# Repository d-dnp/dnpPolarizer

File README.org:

#+TITLE: Dissolution-DNP Polarizer at Southampton University

* Project description
Dissolution-Dynamic Nuclear Polarization (d-DNP) is a technique to enhance the nuclear magnetic reosonance (NMR) signal of small molecules / metabolites by several orders of magnitude. 

Clinical and pre-clinical systems are available commercially, but are costly and cannot provide the felixibility to implement new experimental procedures.

This repository contains the design of the dissolution-DNP system at Southampton University. We hope that it will become a valuable ressource for people working in the field and would be grateful for external contributions / modifications.

Using Trityl and pyruvic acid, a polarization level of 18 % was achieved.

Using TEMPOL and H2O/d-glycerol, a polarization level of 12 % was achieved on sodium acetate.

* The setup at Southampton

The system operates at 6.7 Tesla and uses an Oxford Instruments Spectrostat flow cryostat and a roots pump.

The key components that we are using are as follows: 
| Component                 | Manufacturer       | Approximate Price (EURO)            |
|---------------------------+--------------------+-------------------------------------|
| 6.7 Tesla SWB Magnet      | Bruker             | 60 k (used WB magnets are suitable) |
| Spectrostat Flow Cryostat | Oxford Instruments | 20 k                                |
| Roots Pump, RUVAC WAU251  | Oerlikon           | 20 k                                |
| 188 GHz Microwave Source  | ELVA               | 20 k                                |
| Mini NMR Spectrometer     | Magritek           | 20 k                                |

The use of the Spectrostat Flow cryostat currently limits the temperature to above 2.1 K in continuous mode and 1.8 K in single-shot mode (hold-time approximately 45 mins). 

Options for cryostats with lower base temperature are currently being explored.

** Custom-built components

In addition to these componets, we have designed and built various pieces of instrumentation, listed below. We will shortly add a README file to each of the corresponding folders to provide further information. The mechanical design was performed in SolidWorks. The control electronics rely on the Arduino platform, for which custom printed-circuit board (PCB) extensions, referred to as shields, have been designed in Eagle. The radio-frequency design has been simulated in Python. The project is documented using Emacs org-mode. 

*** DNP insert and CryoShield
The dnp insert allows to irradiate the sample with microwaves at low temperatures down to 1.6K and measure its polarization by NMR. It also hosts a set of Allen-Bradley resistors attached to a custom-built controller/shield. This shield applies 5V pulses to the resistors and measures their resistance as function of time immediately after the pulse. Currently our insert is equipped with coils for 13C and 1H. The coils are roughly tuned and matched with ATC700B chip capacitors, fine tuning is done at room temperatures using an L-Network of Jennings capacitors 1.5 - 45 pF, and optionally coaxial line stretchers (trombone lines) by Microlab.

*** Dissolution Wand and Controller
The controller for the dissolution wand comprises a 220 V to 110 V transformer, whose output can be connected to a mineral barrel heater on the dissolution wand. It also hosts a custom shield that measures the temperature and pressure within the dissolution wand via simple voltage dividers. Finally the controller hosts a relay board to control the various (pilot) valves in the system, including those that drive the dissolution. 

*** Magnetic Tunnel
Following dissolution the solute is flushed to our 500 MHz liquid-state NMR magnet via a magnetic tunnel to reduce low-field relaxation. Documentation of the tunnel is to follow.

*** Injector
An injector has been designed to fit into our 500 MHz magnet. 

*** Arbitrary Waveform Generator
An arbitrary waveform generator providing an output of up to 24 V has been designed to allow sweeps of the microwave source. We are not using it routinely at the moment, though it is fully functional. 
This device is based on an Arduino Due.

* Procedures
** Sample preparation
More detailed procedures will be in the sample preparation folder.

** Probe tuning
We use an Agilent FieldFox Network Analyser to tune and match our probes. More details will be published soon.

* Acknowledgement
We would like to thank Sami Jannin, Jonas Milani, Jan Hendrik Ardenkjaer-Larsen, Arnaud Comment and Jacques van der Klink for discussions and advice.

* License
#+BEGIN_HTML
<br />This work is licensed under a <a rel="license" href="http://creativecommons.org/licenses/by-sa/3.0/">Creative Commons Attribution-ShareAlike 3.0 Unported License</a>.
#+END_HTML

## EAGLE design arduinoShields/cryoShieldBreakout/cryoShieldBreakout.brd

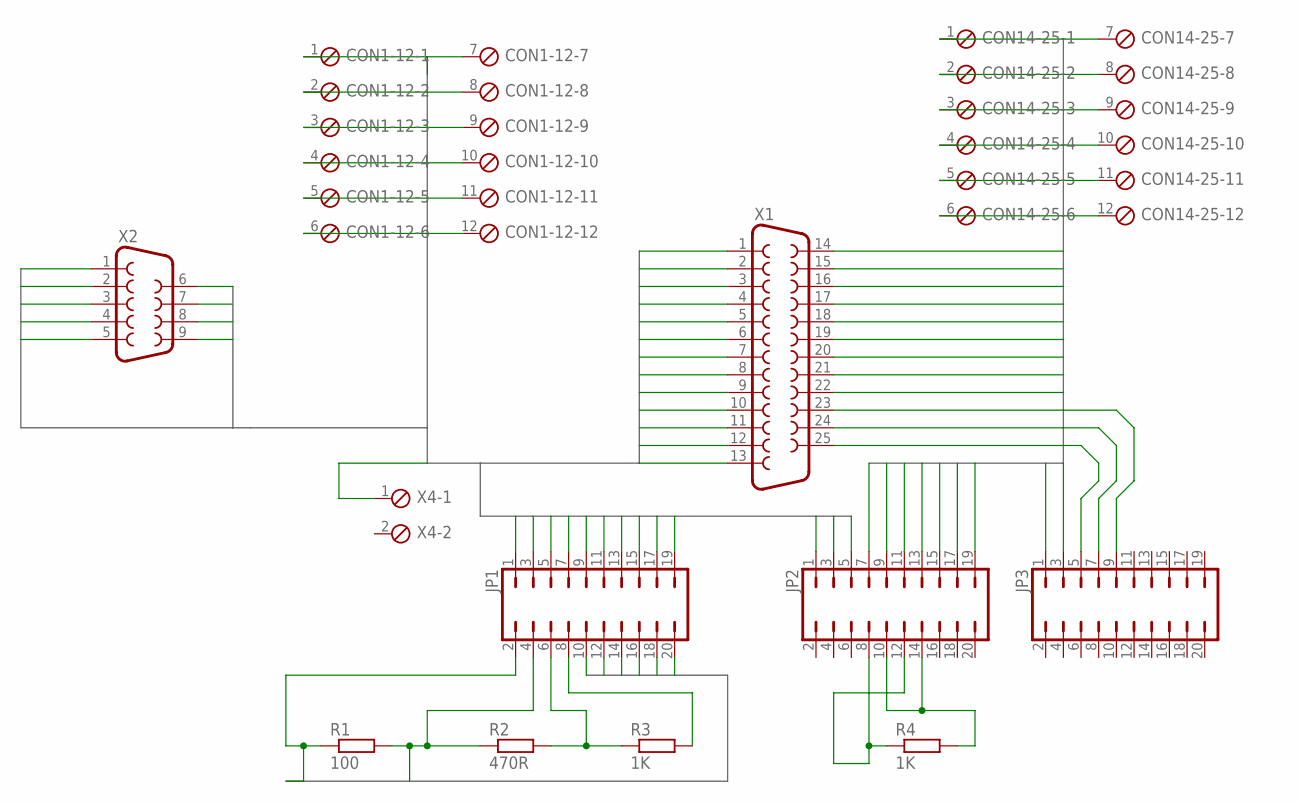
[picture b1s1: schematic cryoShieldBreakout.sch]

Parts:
CON1-12, CON14-25: MPT12; 12POL254
JP1, JP2, JP3: JP10Q
R1: 100; 0207/10
R2: 470R; 0207/10
R3, R4: 1K; 0207/10
X1: F25H
X2: F09H
X4: MPT2; 2POL254

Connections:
1: CON1-12.1, JP1.1, X1.1, X2.1
2: CON1-12.2, JP1.3, X1.2, X2.2
3: CON1-12.3, JP1.5, X1.3, X2.3
4: CON1-12.4, JP1.7, X1.4, X2.4
5: CON1-12.5, JP1.9, X1.5, X2.5
6: CON1-12.6, JP1.11, X1.6, X2.6
7: CON1-12.7, JP1.13, X1.7, X2.7
8: CON1-12.8, JP1.15, X1.8, X2.8
9: CON1-12.9, JP1.17, X1.9, X2.9
10: CON1-12.10, JP1.19, X1.10
11: CON1-12.11, JP2.1, X1.11
12: CON1-12.12, JP2.3, X1.12
13: JP2.5, X1.13, X4.1
14: CON14-25.1, JP2.7, X1.14
15: CON14-25.2, JP2.9, X1.15
16: CON14-25.3, JP2.11, X1.16
17: CON14-25.4, JP2.13, X1.17
18: CON14-25.5, JP2.15, X1.18
19: CON14-25.6, JP2.17, X1.19
20: CON14-25.7, JP2.19, X1.20
21: CON14-25.8, JP3.1, X1.21
22: CON14-25.9, JP3.3, X1.22
23: CON14-25.10, JP3.5, X1.23
24: CON14-25.11, JP3.7, X1.24
25: CON14-25.12, JP3.9, X1.25
A1+: JP1.2, JP1.10, R1.1
A1-: JP1.4, R1.2, R2.1
A2+: JP1.12, JP1.14
A3+: JP1.16, JP1.18
A3-: JP1.20
unnamed: JP2.8, JP2.12, R4.1
unnamed: JP2.10, JP2.14, R4.2
unnamed: JP1.6, R2.2, R3.1
unnamed: JP1.8, R3.2

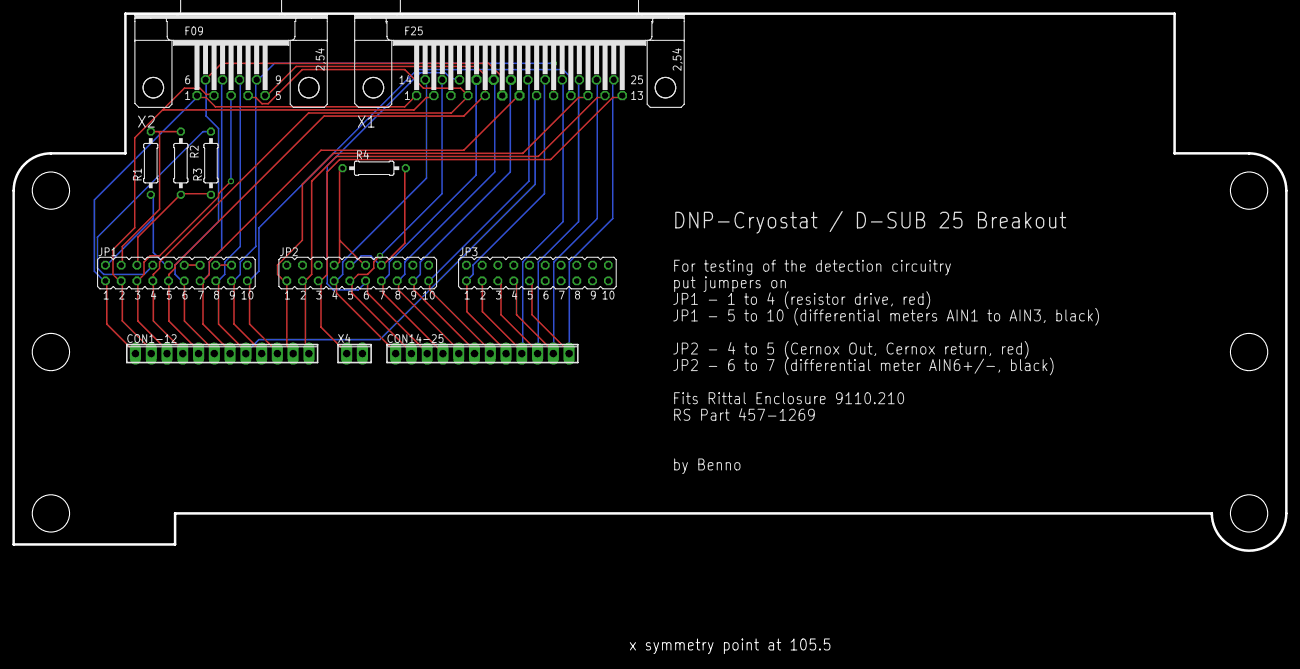
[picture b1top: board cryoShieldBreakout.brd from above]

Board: 2 copper layers, 205.0 x 86.5 mm, 12 parts (0 on the bottom side), 33 nets.

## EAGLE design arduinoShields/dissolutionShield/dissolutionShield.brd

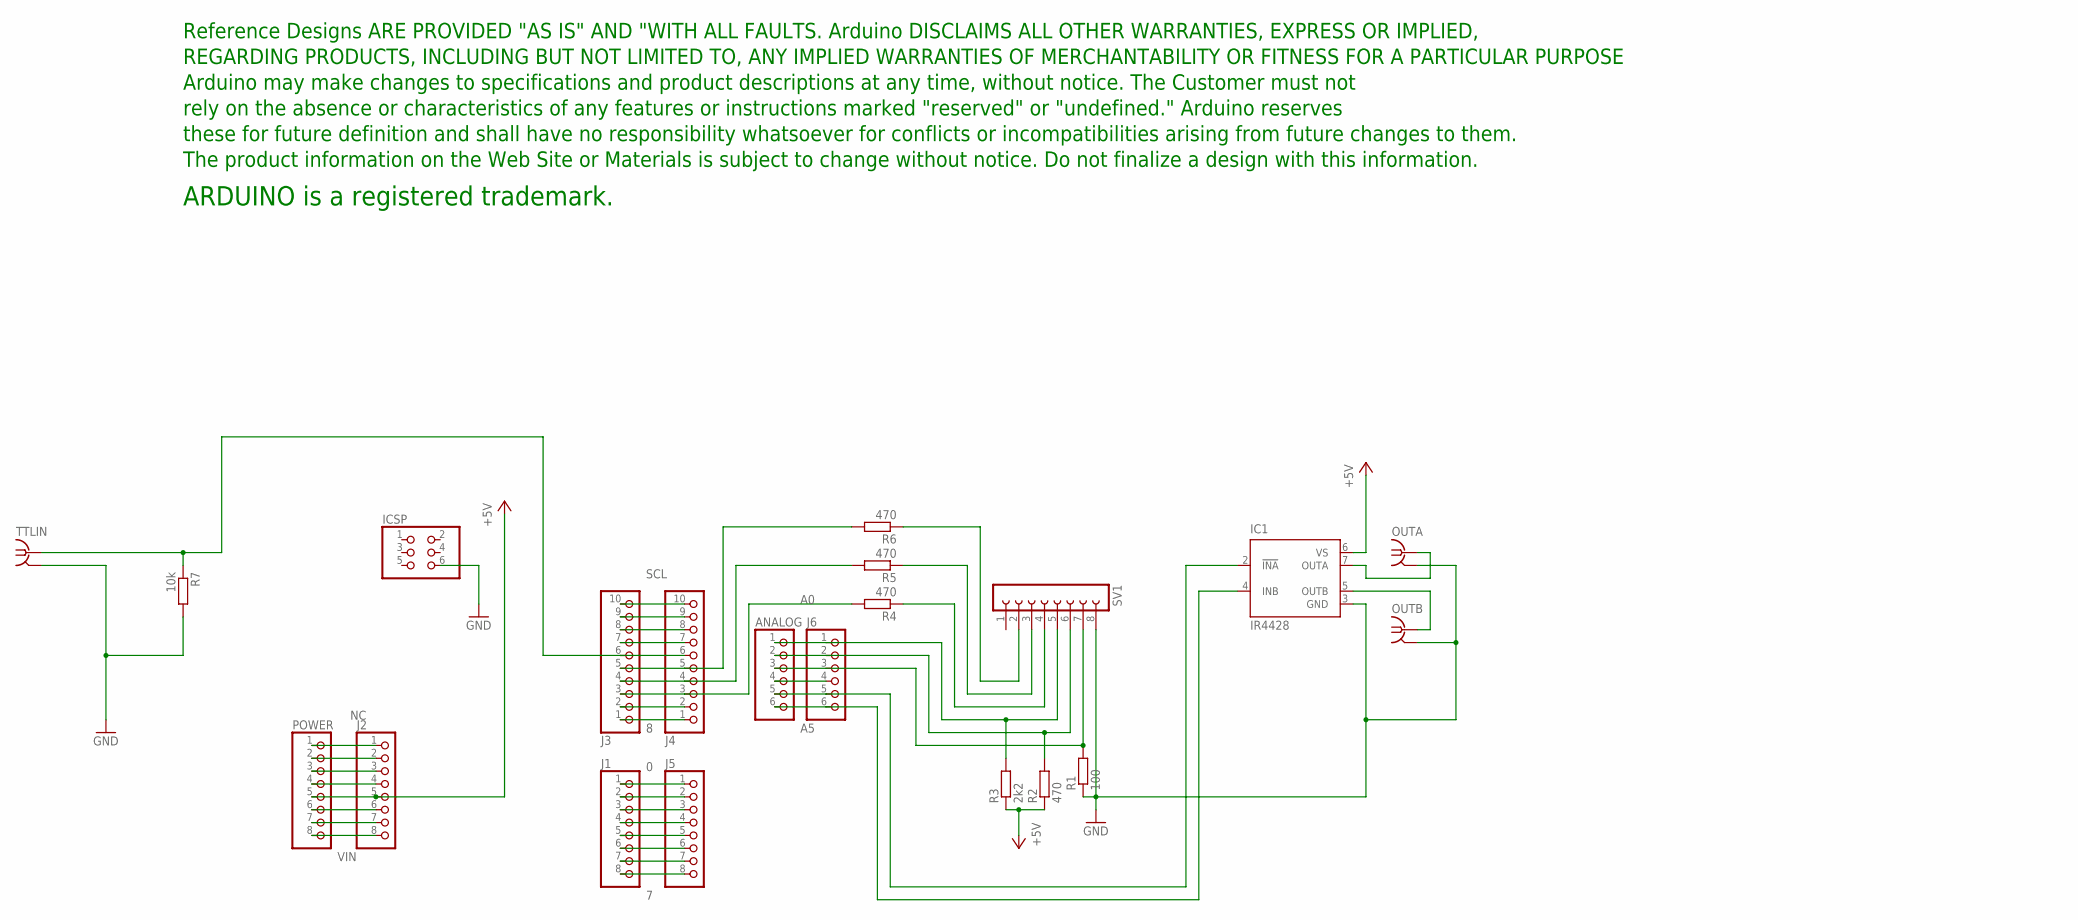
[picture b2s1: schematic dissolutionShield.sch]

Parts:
ANALOG: PINHD-1X6; 1X06
IC1: IR4428; DIL08
ICSP: PINHD-2X3; 2X03
J1, J2, J5: PINHD-1X8TH; 1X08-TH
J3, J4: PINHD-1X10TH; 1X10-TH
J6: PINHD-1X6; 1X06
OUTA: BU-SMA-H
OUTB: BU-SMA-H
POWER: PINHD-1X8TH; 1X08-TH
R1: 100; 0207/10
R2, R4, R5, R6: 470; 0207/10
R3: 2k2; 0207/10
R7: 10k; 0207/10
SV1: FE08-1; FE08
TTLIN: BU-SMA-H
U$1: DISCLAIMER

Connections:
0: J1.1, J5.1
1: J1.2, J5.2
2: J1.3, J5.3
3: J1.4, J5.4
4: J1.5, J5.5
5: J1.6, J5.6
6: J1.7, J5.7
7: J1.8, J5.8
8: J3.1, J4.1
9: J3.2, J4.2
10: J3.3, J4.3, R4.2
11: J3.4, J4.4, R5.2
+3V3: J2.4, POWER.4
+5V: IC1.6 (VS), J2.5, POWER.5, R2.1, R3.1
A0: ANALOG.1, J6.1, R3.2, SV1.5
A1: ANALOG.2, J6.2, R2.2, SV1.6
A2: ANALOG.3, J6.3, R1.2, SV1.7
A3: ANALOG.4, J6.4
A4: ANALOG.5, IC1.2 (!INA), J6.5
A5: ANALOG.6, IC1.4 (INB), J6.6
AREF: J3.8, J4.8
GND: IC1.3 (GND), ICSP.6, J2.6, J2.7, J3.7, J4.7, OUTA.2, OUTA.3 (2), OUTA.4 (2), OUTA.5 (2), OUTB.2, OUTB.3 (2), OUTB.4 (2), OUTB.5 (2), POWER.6, POWER.7, R1.1, R7.2, SV1.8, TTLIN.2, TTLIN.3 (2), TTLIN.4 (2), TTLIN.5 (2)
IOREF: J2.2, POWER.2
N12: J3.5, J4.5, R6.2
N13: J3.6, J4.6, R7.1, TTLIN.1
unnamed: IC1.7 (OUTA), OUTA.1
unnamed: IC1.5 (OUTB), OUTB.1
unnamed: R4.1, SV1.4
unnamed: R5.1, SV1.3
unnamed: R6.1, SV1.2
NC: J2.1, POWER.1
RESET: J2.3, POWER.3
SCL: J3.10, J4.10
SDA: J3.9, J4.9
VIN: J2.8, POWER.8

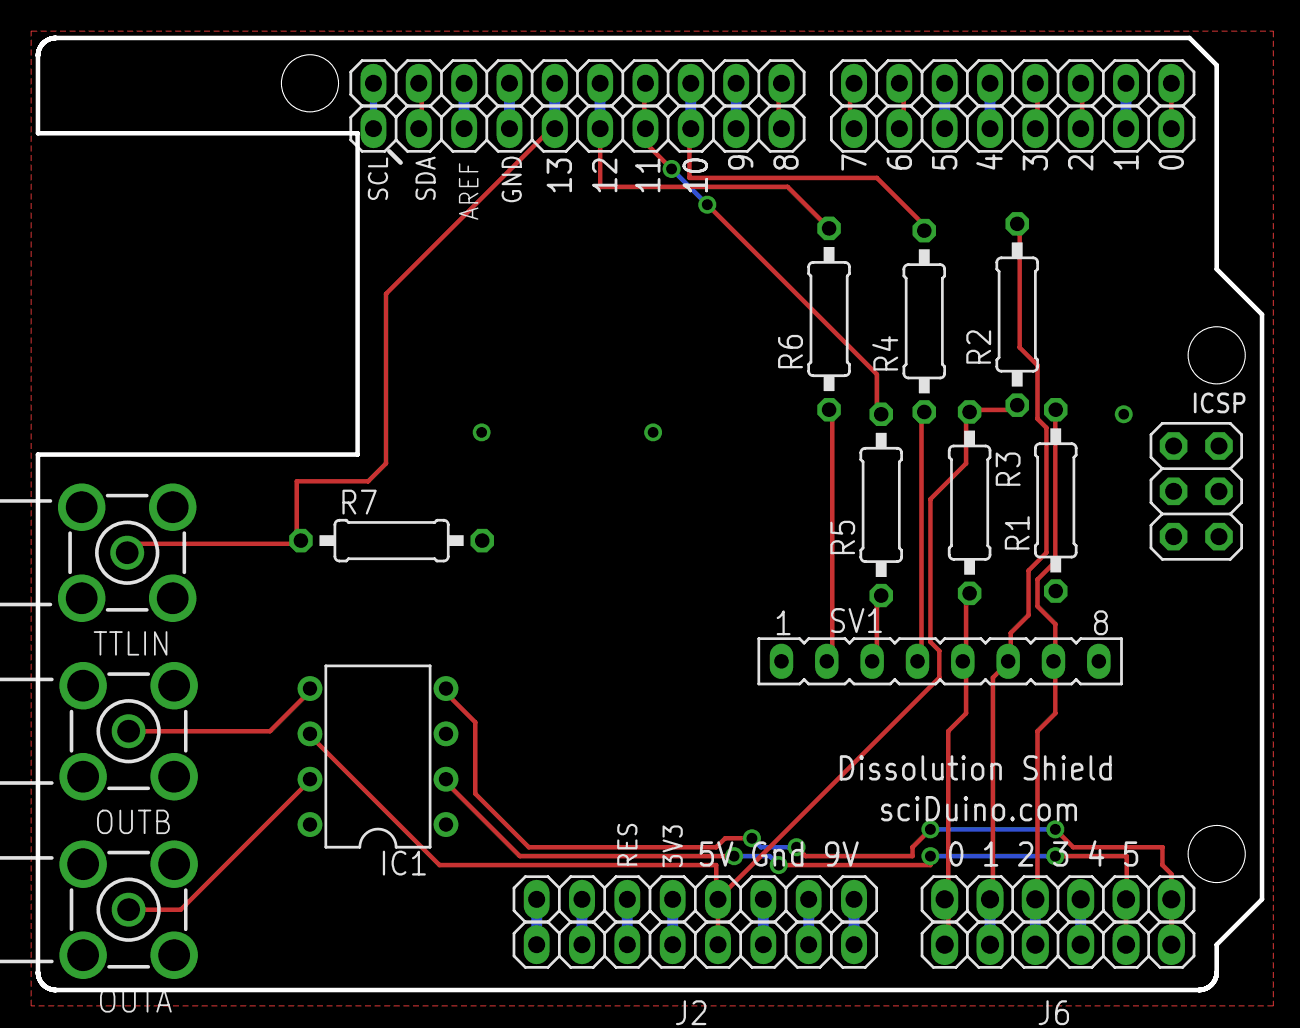
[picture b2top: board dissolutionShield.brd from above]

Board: 2 copper layers, 68.6 x 53.3 mm, 22 parts (0 on the bottom side), 35 nets.

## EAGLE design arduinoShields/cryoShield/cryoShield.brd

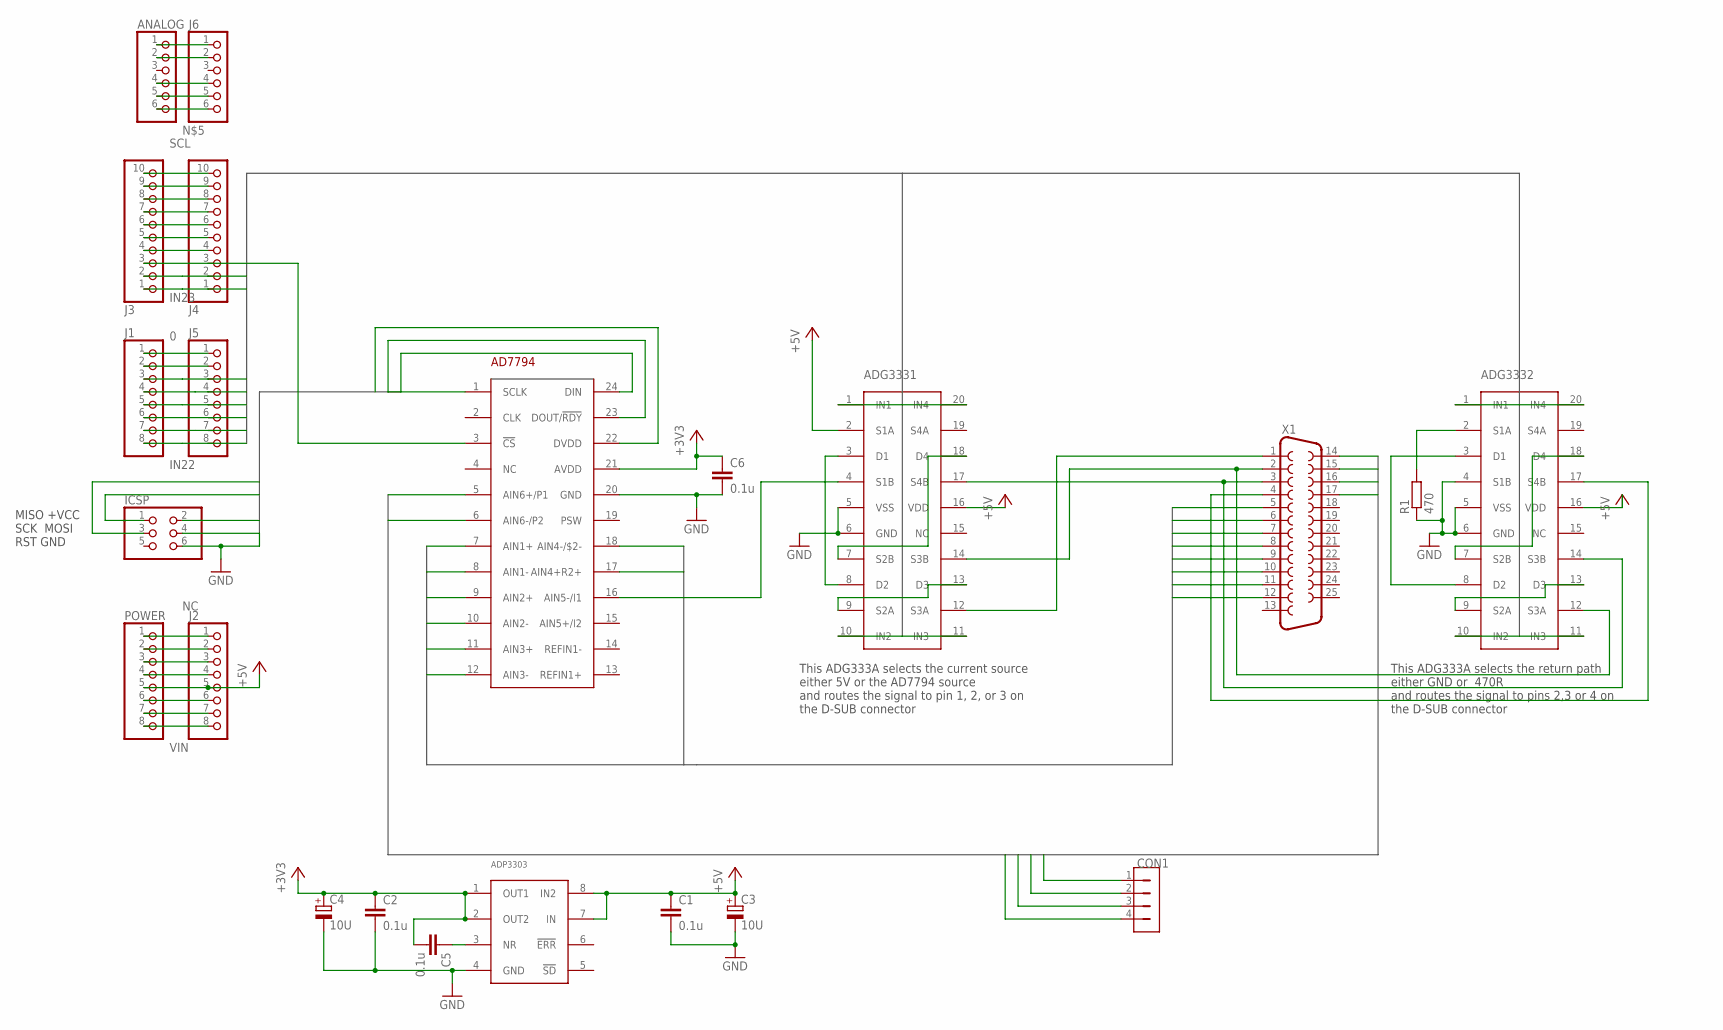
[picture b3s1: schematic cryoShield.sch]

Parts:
AD7794: AD7794; TSSOP24
ADG3331, ADG3332: ADG333; SOIC20S
ADP3303: ADP3303; SOIC8
ANALOG: PINHD-1X6; 1X06
C1, C2, C5, C6: 0.1u; C0805
C3, C4: 10U; CPOL1206
CON1: MICROCLASP4
ICSP: PINHD-2X3; 2X03
J1, J2, J5: PINHD-1X8TH; 1X08-TH
J3, J4: PINHD-1X10TH; 1X10-TH
J6: PINHD-1X6; 1X06
POWER: PINHD-1X8TH; 1X08-TH
R1: 470; 0207/10
X1: F25H

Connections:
0: J1.1, J5.1
1: J1.2, J5.2
+3V3: AD7794.21 (AVDD), ADP3303.1 (OUT1), ADP3303.2 (OUT2), C2.1, C4.1 (+), C5.2, C6.1, J2.4, POWER.4
+5V: ADG3331.2 (S1A), ADG3331.16 (VDD), ADG3332.16 (VDD), ADP3303.7 (IN), ADP3303.8 (IN2), C1.1, C3.1 (+), J2.5, POWER.5
A0: ANALOG.1, J6.1
A1: ANALOG.2, J6.2
A3: ANALOG.4, J6.4
ADG3332: ADG3332.7 (S2B), ADG3332.18 (D4)
AIN1+: AD7794.7 (AIN1+), X1.5
AIN1-: AD7794.8 (AIN1-), X1.6
AIN2+: AD7794.9 (AIN2+), X1.7
AIN2-: AD7794.10 (AIN2-), X1.8
AIN3+: AD7794.11 (AIN3+), X1.9
AIN3-: AD7794.12 (AIN3-), X1.10
AIN4+: AD7794.17 (AIN4+R2+), X1.11
AIN4-: AD7794.18 (AIN4-/$2-), X1.12
AIN6+: AD7794.5 (AIN6+/P1), CON1.3, X1.16
AIN6-: AD7794.6 (AIN6-/P2), CON1.4, X1.17
CERNOXHIGH: CON1.1, X1.14
CERNOXLOW: CON1.2, X1.15
GND: AD7794.20 (GND), ADG3331.5 (VSS), ADG3331.6 (GND), ADG3332.4 (S1B), ADG3332.5 (VSS), ADG3332.6 (GND), ADP3303.4 (GND), C1.2, C2.2, C3.2 (-), C4.2 (-), C6.2, ICSP.6, J2.6, J2.7, J3.7, J4.7, POWER.6, POWER.7, R1.1
IN11: ADG3331.1 (IN1), J1.3, J5.3
IN12: ADG3331.10 (IN2), J1.4, J5.4
IN13: ADG3331.11 (IN3), J1.5, J5.5
IN14: ADG3331.20 (IN4), J1.6, J5.6
IN21: ADG3332.1 (IN1), J1.7, J5.7
IN22: ADG3332.10 (IN2), J1.8, J5.8
IN23: ADG3332.11 (IN3), J3.1, J4.1
IN24: ADG3332.20 (IN4), J3.2, J4.2
IOREF: J2.2, POWER.2
MISO: AD7794.23 (DOUT/!RDY), ICSP.1
MOSI: AD7794.24 (DIN), ICSP.4
unnamed: ADG3331.14 (S3B), ADG3332.12 (S3A), X1.2
unnamed: ADG3331.3 (D1), ADG3331.8 (D2)
unnamed: ANALOG.5, J6.5
unnamed: ANALOG.6, J6.6
unnamed: ADG3331.9 (S2A), ADG3331.13 (D3)
unnamed: ADG3331.7 (S2B), ADG3331.18 (D4)
unnamed: ADG3331.12 (S3A), X1.1
unnamed: ADG3331.17 (S4B), ADG3332.14 (S3B), X1.3
unnamed: ADG3332.2 (S1A), R1.2
unnamed: ADG3332.3 (D1), ADG3332.8 (D2)
unnamed: ADG3332.9 (S2A), ADG3332.13 (D3)
unnamed: AD7794.16 (AIN5-/I1), ADG3331.4 (S1B)
unnamed: ADP3303.3 (NR), C5.1
unnamed: ADG3332.17 (S4B), X1.4
unnamed: AD7794.3 (!CS), J3.3, J4.3
unnamed: J3.4, J4.4
unnamed: J3.5, J4.5
unnamed: J3.6, J4.6
unnamed: J3.8, J4.8
NC: J2.1, POWER.1
RESET: J2.3, POWER.3
SCK: AD7794.1 (SCLK), ICSP.3
SCL: J3.10, J4.10
SDA: J3.9, J4.9
VCC: AD7794.22 (DVDD), ICSP.2
VIN: J2.8, POWER.8

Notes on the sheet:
This ADG333A selects the current source either 5V or the AD7794 source and routes the signal to pin 1, 2, or 3 on the D-SUB connector
This ADG333A selects the return path either GND or 470R and routes the signal to pins 2,3 or 4 on the D-SUB connector
MISO +VCC SCK MOSI RST GND

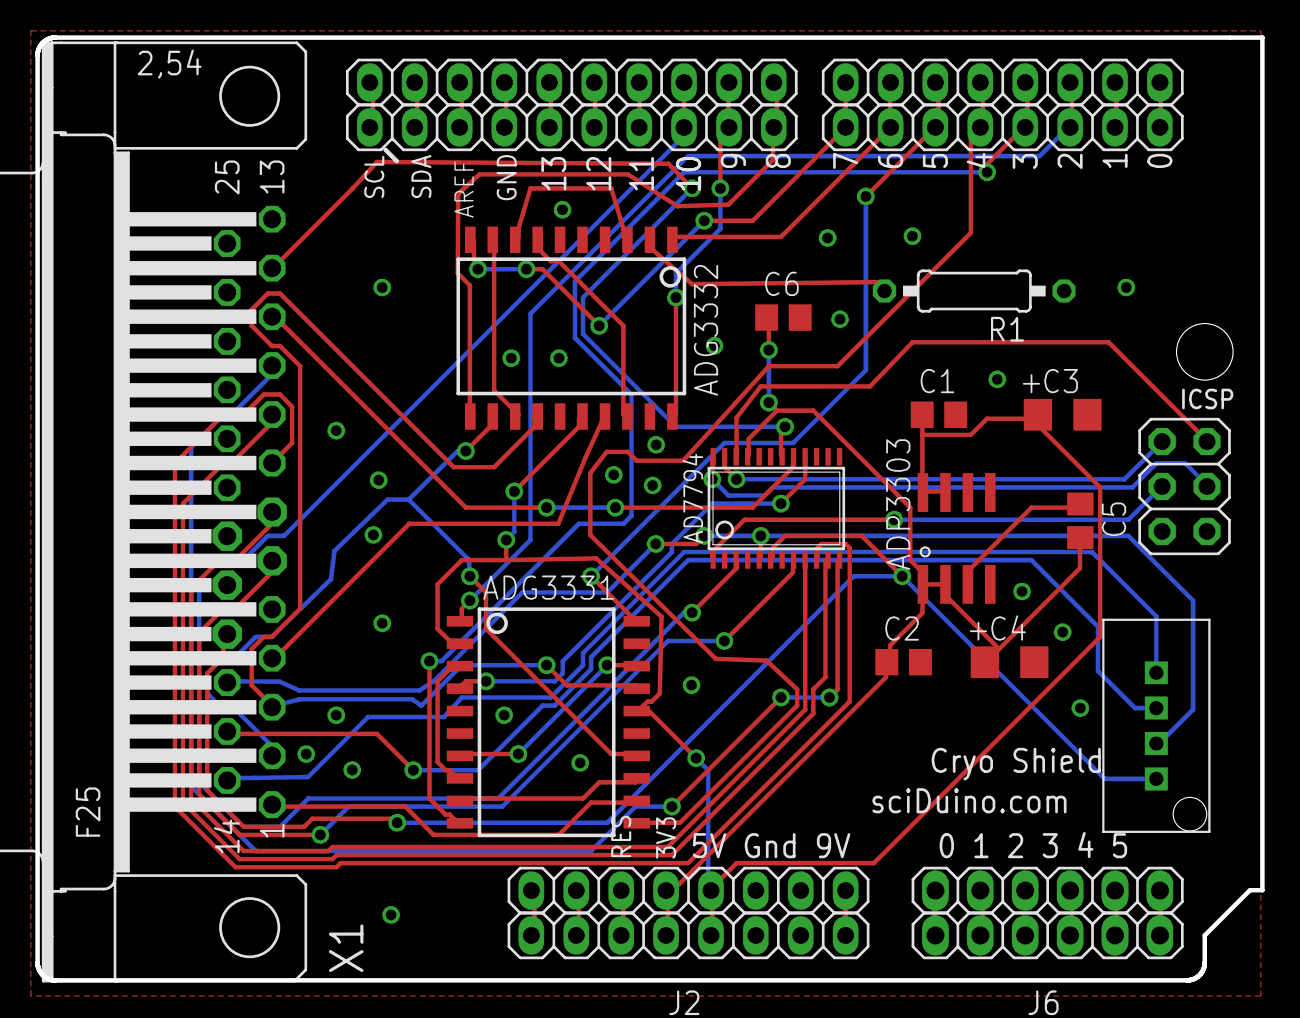
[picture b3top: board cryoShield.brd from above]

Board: 2 copper layers, 69.3 x 53.3 mm, 22 parts (0 on the bottom side), 58 nets.

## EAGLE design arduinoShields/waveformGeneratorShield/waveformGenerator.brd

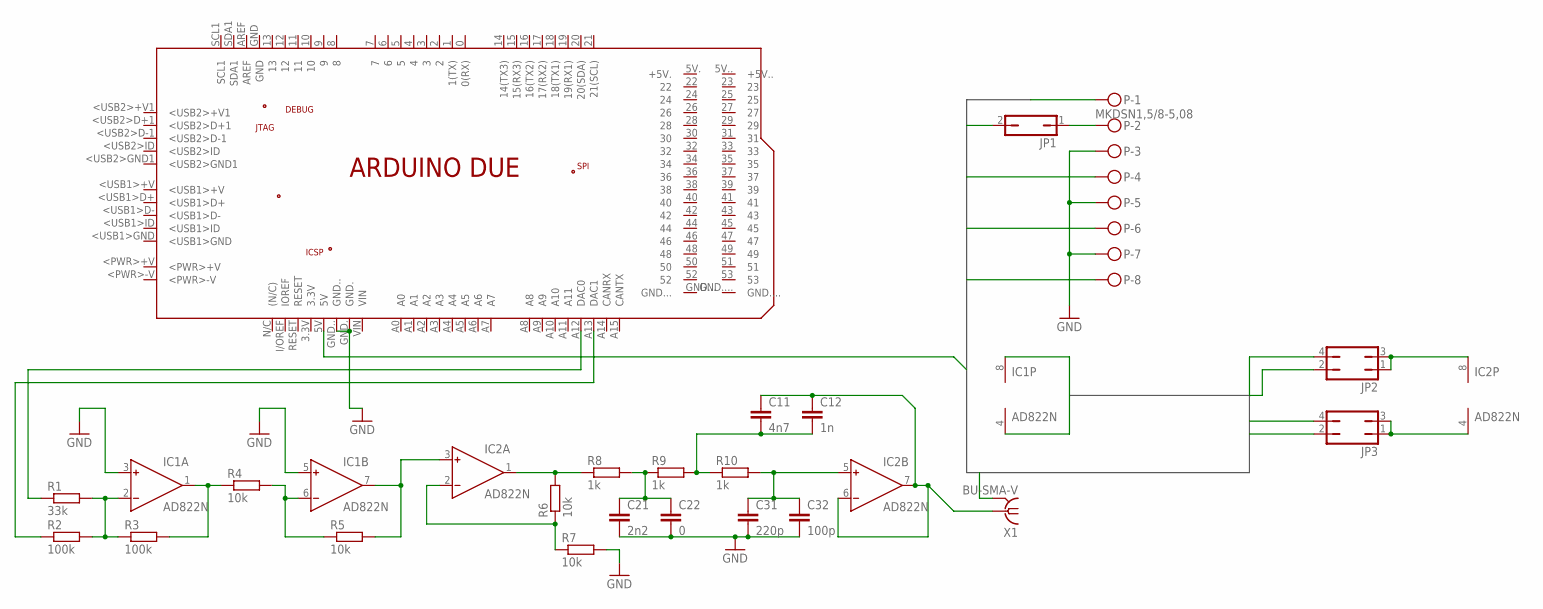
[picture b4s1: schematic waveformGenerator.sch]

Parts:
C11: 4n7; C050-030X075
C12: 1n; C050-030X075
C21: 2n2; C050-030X075
C22: 0; C050-030X075
C31: 220p; C050-030X075
C32: 100p; C050-030X075
IC1, IC2: AD822N; DIL08
JP1: JP1Q; JP1
JP2, JP3: JP2Q
P: MKDSN1,5/8-5,08
PCB1: ARDUINO_DUE
R1: 33k; 0207/10
R2, R3: 100k; 0207/10
R4, R5, R6, R7: 10k; 0207/10
R8, R9, R10: 1k; 0207/10
X1: BU-SMA-V

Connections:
+5: JP1.2, PCB1.5V
+15: IC1.8 (V+), JP2.2, P.8
+24: JP2.4, P.4
-15: IC1.4 (V-), JP3.2, P.6
GND: C21.2, C22.2, C31.2, C32.2, IC1.3 (IN+), IC1.5 (IN+), JP3.4, P.1, P.3, P.5, P.7, PCB1.GND., PCB1.GND.., R7.2, X1.2, X1.3 (2), X1.4 (2), X1.5 (2)
unnamed: PCB1.A12 (DAC0), R1.1
unnamed: PCB1.A13 (DAC1), R2.1
unnamed: IC1.2 (IN-), R1.2, R2.2, R3.1
unnamed: JP1.1, P.2
unnamed: IC1.1 (OUT), R3.2, R4.1
unnamed: IC1.6 (IN-), R4.2, R5.1
unnamed: IC1.7 (OUT), IC2.3 (IN+), R5.2
unnamed: IC2.4 (V-), JP3.1, JP3.3
unnamed: IC2.8 (V+), JP2.1, JP2.3
unnamed: C11.1, C12.1, IC2.6 (IN-), IC2.7 (OUT), X1.1
unnamed: IC2.2 (IN-), R6.1, R7.1
unnamed: IC2.1 (OUT), R6.2, R8.1
unnamed: C21.1, C22.1, R8.2, R9.1
unnamed: C11.2, C12.2, R9.2, R10.1
unnamed: C31.1, C32.1, IC2.5 (IN+), R10.2

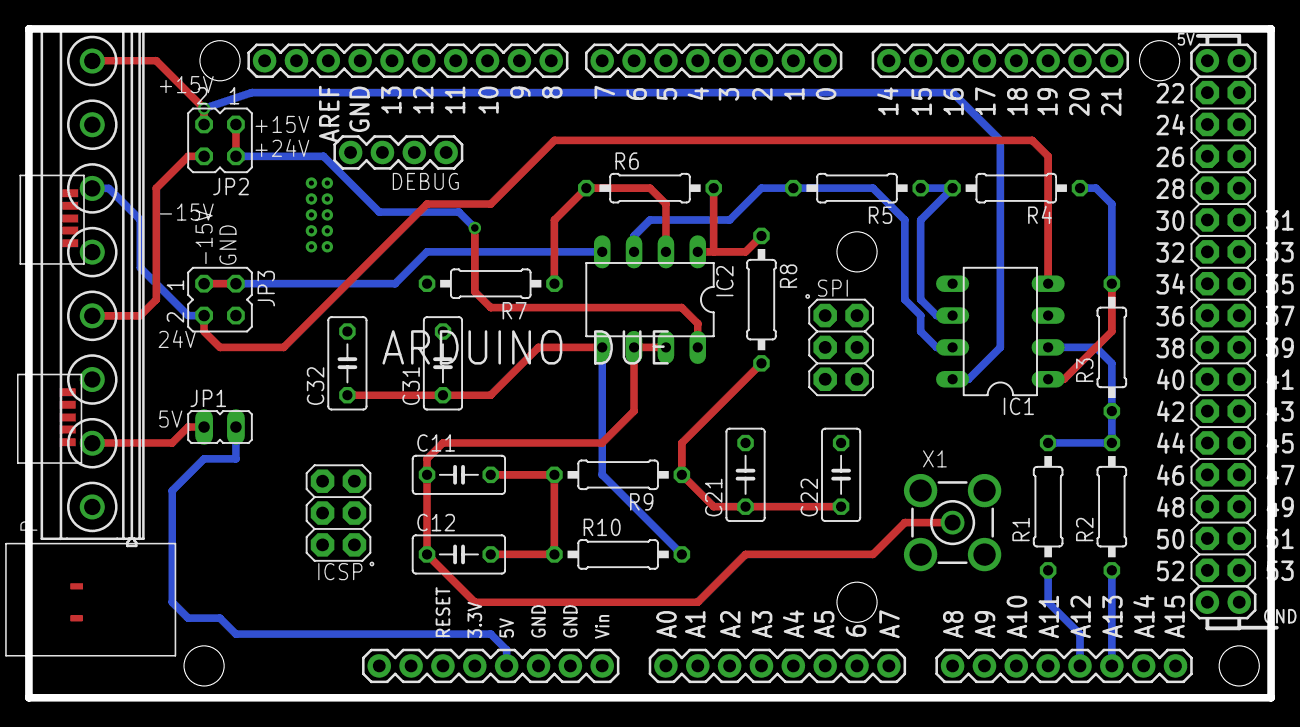
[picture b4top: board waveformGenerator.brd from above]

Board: 2 copper layers, 99.1 x 53.3 mm, 24 parts (0 on the bottom side), 20 nets.

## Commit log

2016-07-01 Initial commit for GitHub.
2016-07-01 Updated README.org
2016-07-04 Fixed Software Folder
2016-09-08 Added magnetic tunnel information, updated README
2016-09-09 Change magnetic tunel description from .rtf to .md
2016-09-09 magnetic tunnel information renamed README
2016-09-09 Changed README.md to README.org
2016-09-09 edit README.org
2016-09-11 Add simple temperatureMonitor script for Mercury Temperature Controller
2016-09-29 Changes to software/mercuryMonitor.py
2016-12-10 Minor software changes, add drawings
2016-12-10 Restructure dnpInsert folder
